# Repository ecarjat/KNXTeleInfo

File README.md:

# **French energy provider Enedis TeleInfo (TIC) KNX interface.**

Compatible with Enedis Linky meters in "Historic" mode, and "Blue" meters.

This is a fork of [etrinh software](https://github.com/etrinh/TeleInfoKNX) whose original design can be bought [here](https://www.tindie.com/products/zdi/knx-teleinfo/) 

This fork uses Raspberry [RP2040](https://www.raspberrypi.com/products/rp2040/) with a 64M-bit Serial Flash Memory and has a USB B Micro port to update the firmware.

# Firmware

The firmware has been refactored to split classes into their own files and adapt it to the rp2040.
It also leverages the latest version (as of 01/12/22) of [KNX Library](https://github.com/thelsing/knx) and in particular it's support for RP2040.

## **Features:**
- Activatable RealTime mode for real-time consumption monitoring/display.
- History of total Consumption (Current Year, Current Month, Today, Last Year, Last Month, Yesterday) (an external KNX Clock participant is required to provide accurate date and time).
- ETS5 configurable.
- Bus powered (10mA).

## **Usage:**
- Connect the device to the TeleInfo terminals (I1 I2) on the energy meter (No polarity).
- Connect the device to the KNX bus.
- To activate the device Programming Mode, click the "PROG / HRST".
- Configure device in ETS.
- To reset History, press the History Reset "PROG / HRST" Button more than 4 seconds.
- In case of over-current warning, the message "Depassement" (Group Object 43) is repeated every 10 seconds on the bus.

## **Led Interpretation:**
- Led Blinking (0.5s On/1.5s Off): TeleInfo data are receiving - **Device is working properly**.
- Led Continuously On: The device is in programming mode (it will automatically switch off after a delay of 15 minutes or a new press on the "PROG / HRST" button).
- Led Blinking (0.5s On/0.5s Off): The History is erased (happens when the "PROG / HRST" Button is pressed during more than 4 seconds).
- Led Off: The device is not receiving TeleInfo data, or is not configured with ETS5, or is not connected to the KNX Bus.

## **Group Objects:**
All "Consumption" Group Objects (from GO 7 to GO 24):

- Can be read to get the consumption index difference from the beginning and ending of the specified period.
- Can be written by the consumption index at the beginning of the corresponding period. It allows to specifically initialize the history from data provided by your energy provider. It is advised to set these indexes before affecting monitoring participants to these Group Objects.

## **Product Database:**
Click [here](https://github.com/etrinh/TeleInfoKNX/raw/master/ETS/teleinfo.knxprod) to download ETS5 product database (identified as KNX Association).

# Firmware upload
The Firmware can be uploaded directly through the USB port. On MacOS The firmware upload can be done by uncommenting this line in platform.io:
```
;upload_port = /Volumes/RPI-RP2/
```
This leverages the rp2040 embedded boot firmware. If the drive does not show pushing the reset button on the main board (SW3) while plugging in the usb should make it appear.
Once the firmware has been uploaded once, the serial port should become available.

# Hardware

## Sources
The hardware is build from a set of open source designs
[Adafruit ItsyBitsy rp2040](https://github.com/adafruit/Adafruit-ItsyBitsy-RP2040-PCB)
[Nano BCU](https://gitlab.com/knx-makerstuff/knx_microbcu2/-/wikis/NanoBCU)
[PiTInfo](https://github.com/hallard/teleinfo/tree/master/PiTInfo)
cobbled together on a board that needs to be cut in three parts and assembled.

## Geting the hardware

The folder hardware contain the kicad files and the gerber/bom/cpl files that can be sent to [JLCPCB](https://jlcpcb.com/).
The fabrication output is a board 

## Hardware assembly

The board then needs to be cut in three parts.

The assembly should be fairly self explanatory with teh silk screen. There are two unsused pins on the main board reserver for future use.

Once assembled the board looks like this

And fits into a [DIN Rail Box Size 1 from RS PRO](https://docs.rs-online.com/575c/A700000006545717.pdf). This can be ordered [here](https://fr.rs-online.com/web/p/boitiers-rail-din/1947577?cm_mmc=FR-PLA-DS3A-_-google-_-CSS_FR_FR_Boitiers_%26_coffrets_et_armoires_Whoop-_-(FR:Whoop!)+Bo%C3%AEtiers+rail+DIN-_-1947577&matchtype=&pla-305134126740&gclsrc=ds&gclsrc=ds).

## Remarks

The NeoPixel on the top board is not used by this application and is not powered by the firmware.

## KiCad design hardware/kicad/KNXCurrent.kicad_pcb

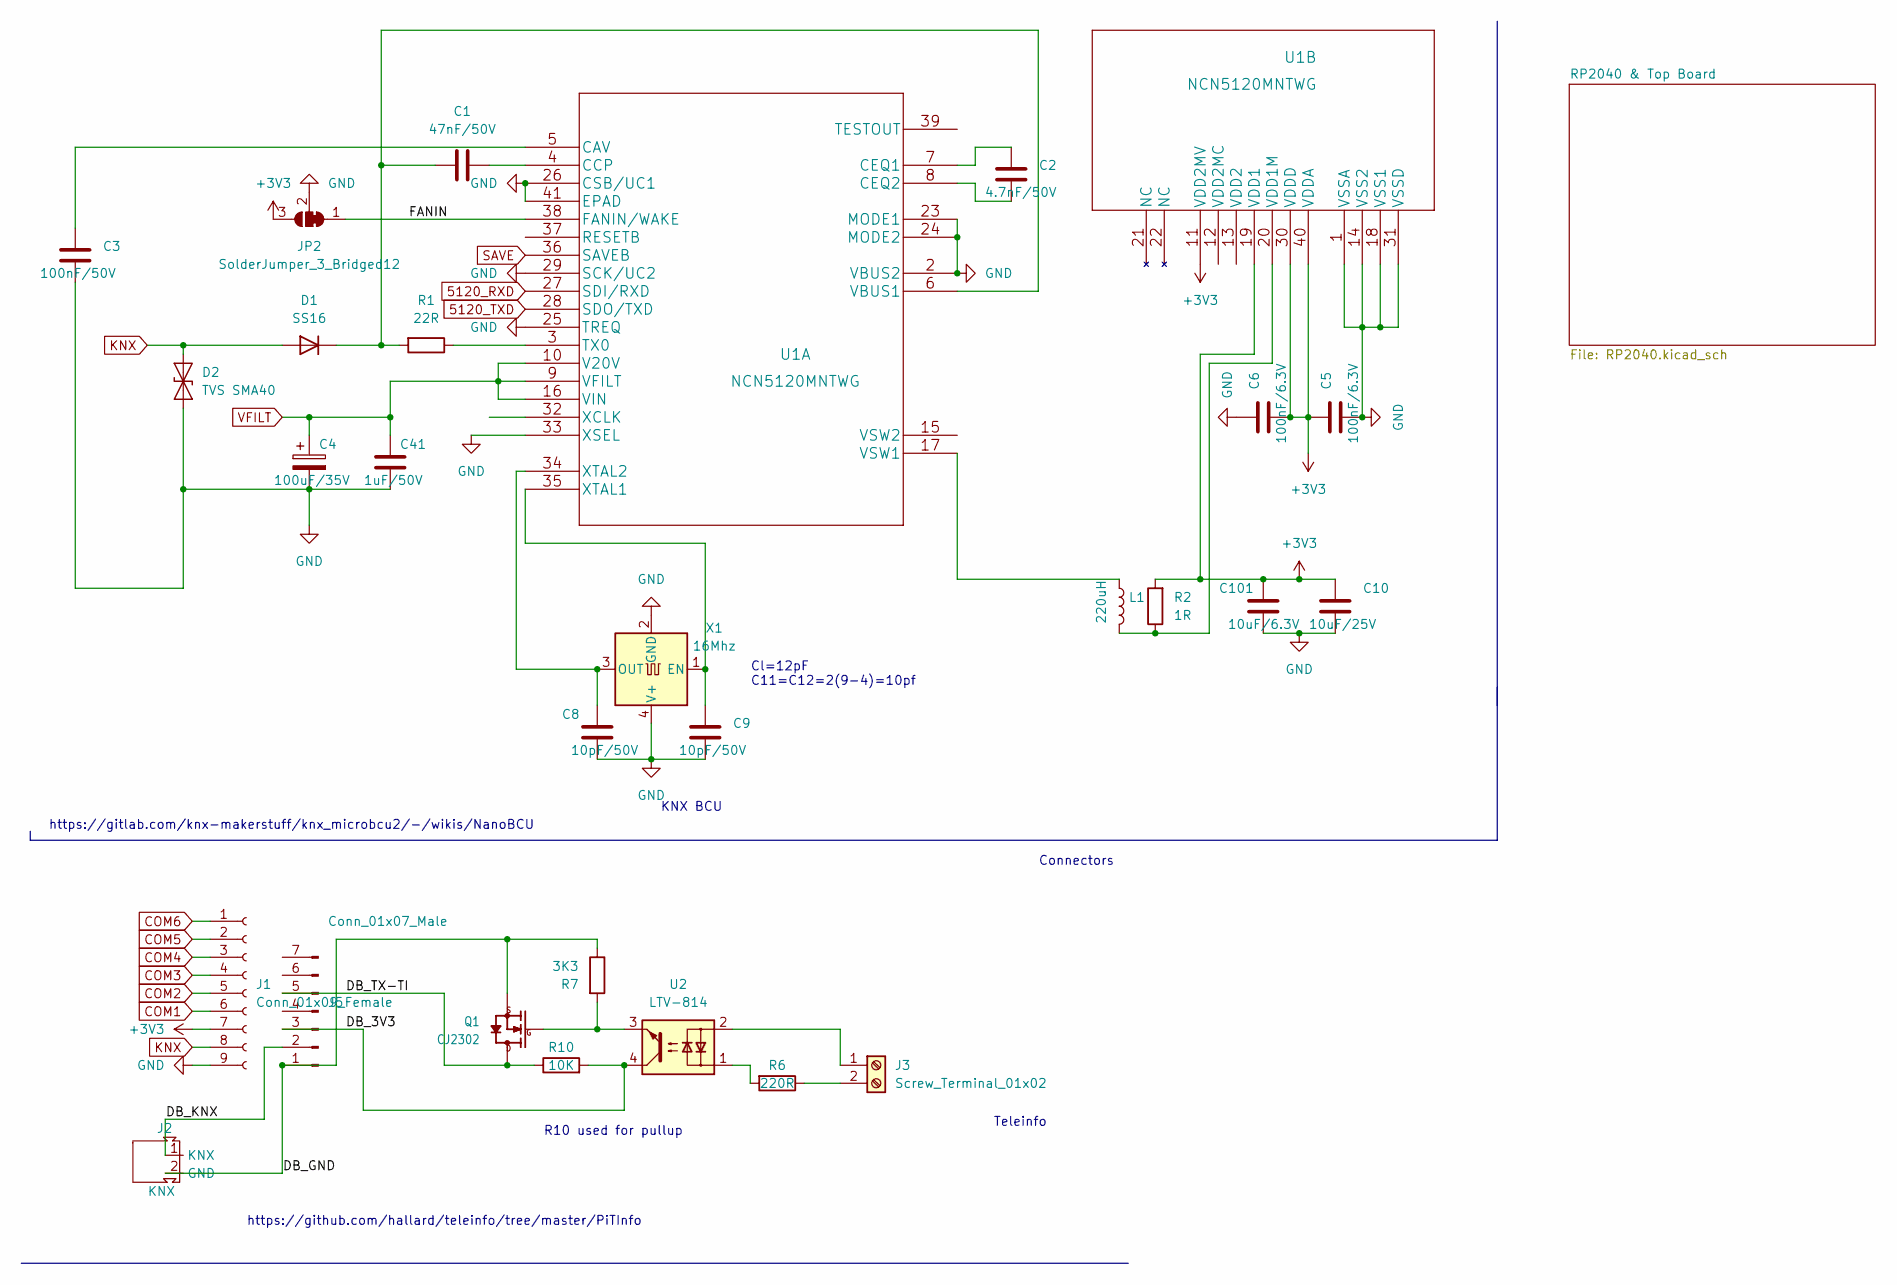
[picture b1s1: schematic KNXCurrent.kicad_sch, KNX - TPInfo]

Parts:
C1: 47nF/50V; C_0603_1608Metric; LCSC C1622
C2: 4.7nF/50V; C_0603_1608Metric; LCSC C53987
C3: 100nF/50V; C_0603_1608Metric; LCSC C14663
C4: 100uF/35V; CP_Elec_6.3x5.7; LCSC C249982
C5, C6: 100nF/6.3V; C_0402_1005Metric; LCSC C1525
C8, C9: 10pF/50V; C_0402_1005Metric; LCSC C32949
C10: 10uF/25V; C_0603_1608Metric; LCSC C96446
C41: 1uF/50V; C_0603_1608Metric; LCSC C15849
C101: 10uF/6.3V; C_0805_2012Metric; LCSC C15850
D1: SS16; D_SMA; LCSC C183023
D2: TVS SMA40; D_SMA; LCSC C513490
J1: Conn_01x09_Female; PinSocket_1x09_P2.54mm_Vertical
J2: KNX; KNX Male
J3: Screw_Terminal_01x02; TerminalBlock_Altech_AK300-2_P5.00mm
J5: Conn_01x07_Male; PinHeader_1x07_P2.54mm_Horizontal
JP2: SolderJumper_3_Bridged12; SolderJumper-3_P1.3mm_Bridged2Bar12_RoundedPad1.0x1.5mm_Num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
L1: 220uH; IND_VLS5045EX-3R3N; LCSC C501936
Q1: CJ2302; SOT-23; LCSC C2910175
R1: 22R; R_2512_6332Metric; LCSC C421606
R2: 1R; R_0402_1005Metric; LCSC C332612
R6: 220R; R_0805_2012Metric; LCSC C17557
R7: 3K3; R_0805_2012Metric; LCSC C26010
R10: 10K; R_0805_2012Metric; LCSC C17414
U1: NCN5120MNTWG; QFN-40-1EP_6x6mm_P0.5mm_EP4.6x4.6mm; LCSC C130364
U2: LTV-814; OPTO-SMD4; LCSC C125118
X1: 16Mhz; Crystal_SMD_3225-4Pin_3.2x2.5mm; LCSC C13738

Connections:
5120_RXD: U1.27 (SDI/RXD); also elsewhere on the board
5120_TXD: U1.28 (SDO/TXD); also elsewhere on the board
+3V3: C5.1, C6.2, C10.1, C101.1, J1.7, JP2.3 (B), R2.2, U1.11 (VDD2MV), U1.19 (VDD1), U1.30 (VDDD), U1.40 (VDDA); also elsewhere on the board
/DB_3V3: J5.3, R10.2, U2.4
/DB_GND: J2.2 (GND), J5.1, Q1.2 (S), R7.1
/DB_KNX: J2.1 (KNX), J5.2
/DB_TX-TI: J5.5, Q1.3 (D), R10.1
/FANIN: JP2.1 (A), U1.38 (FANIN/WAKE)
COM1: J1.6; also elsewhere on the board
COM2: J1.5; also elsewhere on the board
COM3: J1.4; also elsewhere on the board
COM4: J1.3; also elsewhere on the board
COM5: J1.2; also elsewhere on the board
COM6: J1.1; also elsewhere on the board
GND: C3.2, C4.2, C5.2, C6.1, C8.2, C9.2, C10.2, C41.2, C101.2, D2.2 (A2), J1.9, JP2.2 (C), U1.1 (VSSA), U1.2 (VBUS2), U1.14 (VSS2), U1.18 (VSS1), U1.23 (MODE1), U1.24 (MODE2), U1.25 (TREQ), U1.26 (CSB/UC1), U1.29 (SCK/UC2), U1.31 (VSSD), U1.33 (XSEL), U1.41 (EPAD), X1.2 (GND), X1.4 (V+); also elsewhere on the board
KNX: D1.2 (A), D2.1 (A1), J1.8
unnamed: C1.1, D1.1 (K), R1.2, U1.6 (VBUS1)
unnamed: C1.2, U1.4 (CCP)
unnamed: C2.1, U1.7 (CEQ1)
unnamed: C2.2, U1.8 (CEQ2)
unnamed: C3.1, U1.5 (CAV)
unnamed: C8.1, U1.34 (XTAL2), X1.3 (OUT)
unnamed: C9.1, U1.35 (XTAL1), X1.1 (EN)
unnamed: J3.1, U2.2
unnamed: J3.2, R6.1
unnamed: L1.1, U1.17 (VSW1)
unnamed: L1.2, R2.1, U1.20 (VDD1M)
unnamed: Q1.1 (G), R7.2, U2.3
unnamed: R1.1, U1.3 (TX0)
unnamed: R6.2, U2.1
SAVE: U1.36 (SAVEB); also elsewhere on the board
VFILT: C4.1, C41.1, U1.9 (VFILT), U1.10 (V20V), U1.16 (VIN)

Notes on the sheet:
Connectors
R10 used for pullup
https://github.com/hallard/teleinfo/tree/master/PiTInfo
Teleinfo
Cl=12pF C11=C12=2(9-4)=10pf
KNX BCU
https://gitlab.com/knx-makerstuff/knx_microbcu2/-/wikis/NanoBCU

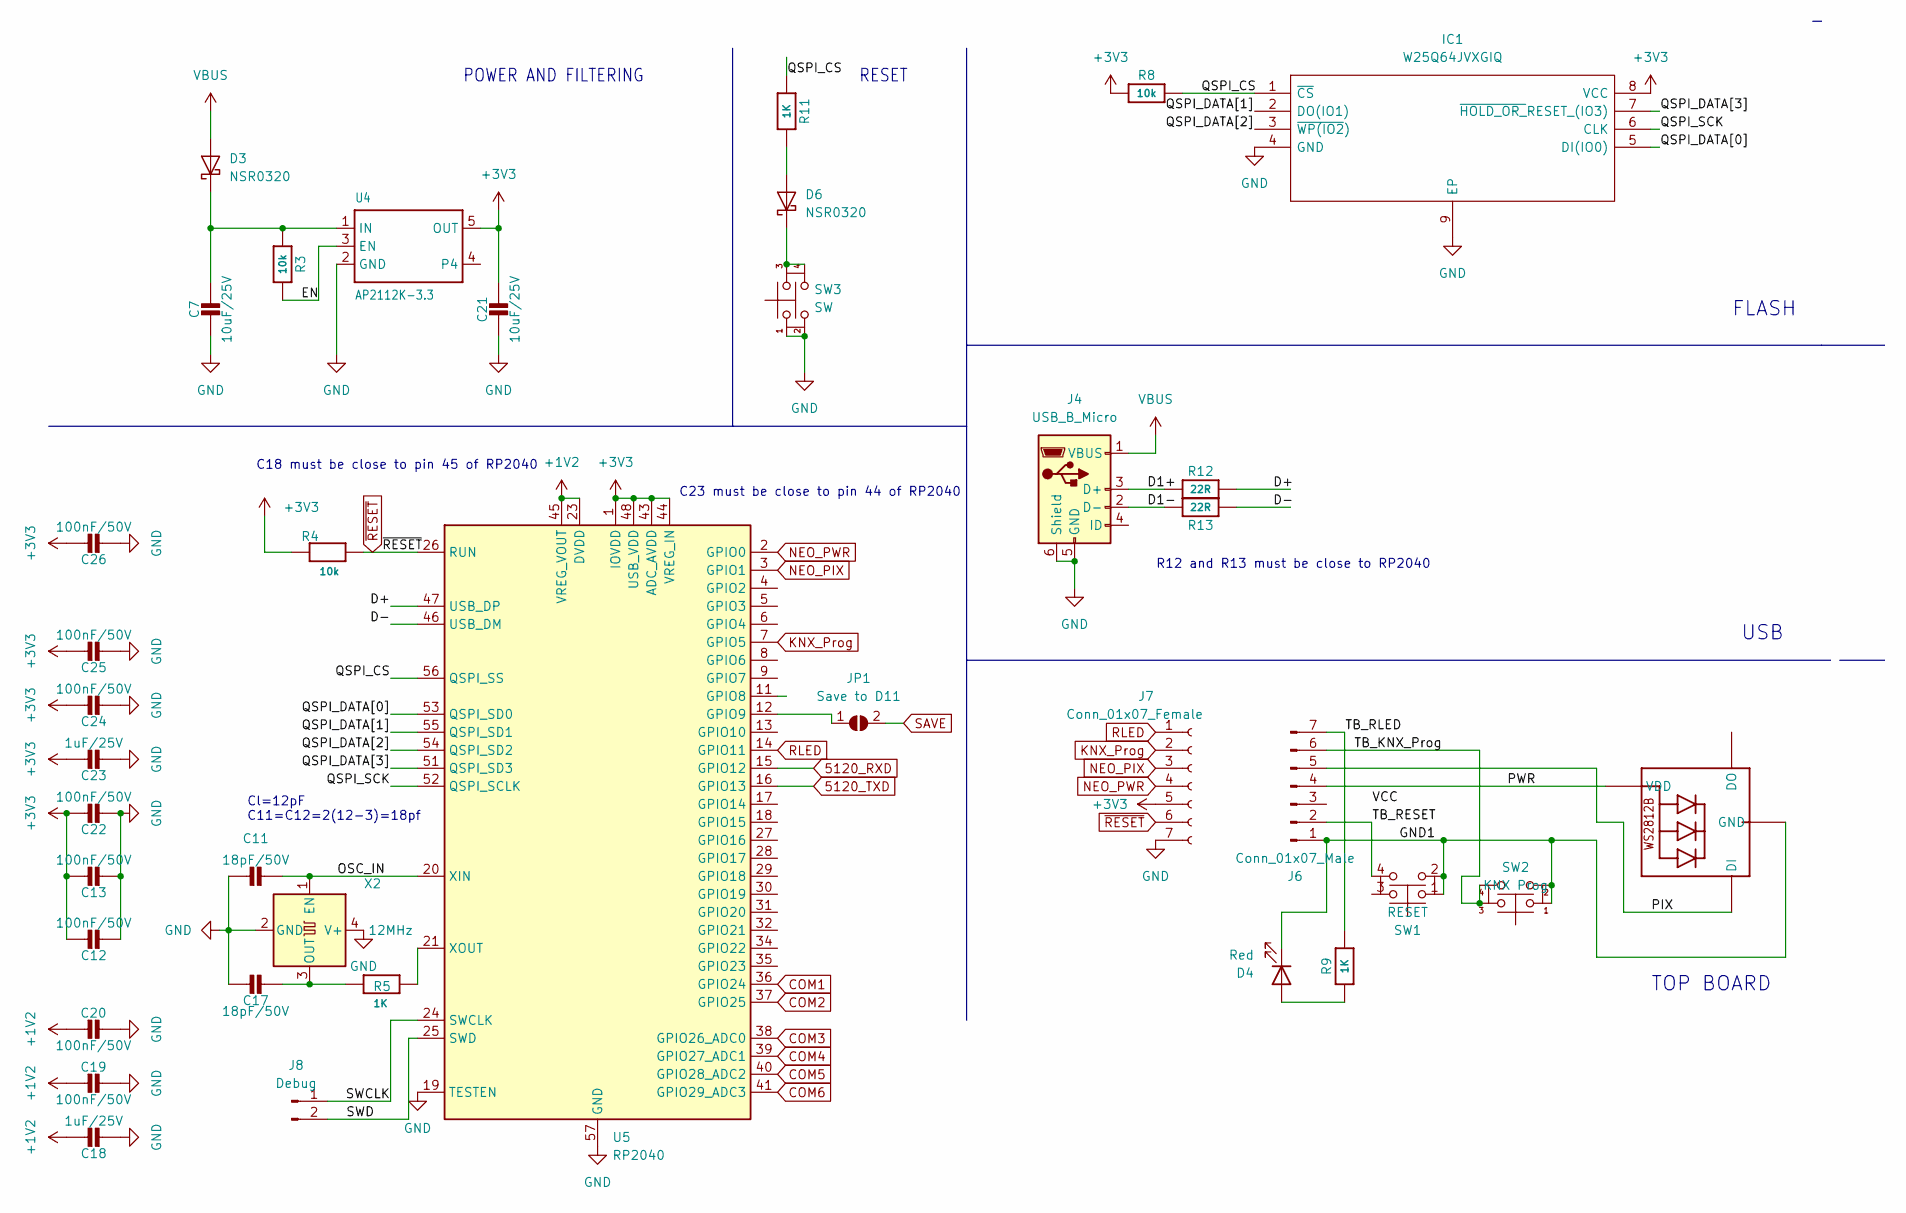
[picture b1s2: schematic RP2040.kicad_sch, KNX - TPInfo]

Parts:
C7, C21: 10uF/25V; C_0603_1608Metric; LCSC C96446
C11, C17: 18pF/50V; C_0402_1005Metric; LCSC C1549
C12, C13, C19, C20, C22, C24, C25, C26: 100nF/50V; C_0402_1005Metric; LCSC C307331
C18, C23: 1uF/25V; C_0402_1005Metric; LCSC C52923
D3, D6: NSR0320; D_SOD-323; LCSC C48192
D4: Red; D_0603_1608Metric; LCSC C2286
IC1: W25Q64JVXGIQ; SON80P400X400X50-9N; Manufacturer_Part_Number W25Q64JVXGIQ; LCSC C2940195
J4: USB_B_Micro; USB_Micro-B_Molex-105017-0001; LCSC C136000
J6: Conn_01x07_Male; PinHeader_1x07_P2.54mm_Horizontal
J7: Conn_01x07_Female; PinSocket_1x07_P2.54mm_Vertical
J8: Debug; PinHeader_1x02_P2.54mm_Vertical
JP1: Save to D11; SolderJumper-2_P1.3mm_Open_RoundedPad1.0x1.5mm
LED1: WS2812B3535; LED_WS2812B_PLCC4_5.0x5.0mm_P3.2mm; LCSC C2920042
R3, R4, R8: 10k; R_0402_1005Metric; LCSC C25744
R5, R9, R11: 1K; R_0402_1005Metric; LCSC C11702
R12, R13: 22R; R_0402_1005Metric; LCSC C25092
SW1: RESET; SW_TS-1187A-B-A-B; LCSC C318884
SW2: KNX Prog; SW_TS-1187A-B-A-B; LCSC C318884
SW3: SW; SW_TS-1187A-B-A-B; LCSC C318884
U4: AP2112K-3.3; SOT-23-5; LCSC C51118
U5: RP2040; QFN-56-1EP_7x7mm_P0.4mm_EP3.2x3.2mm; LCSC C2040
X2: 12MHz; Crystal_SMD_2520-4Pin_2.5x2.0mm; LCSC C521567

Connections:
5120_RXD: U5.15 (GPIO12); also elsewhere on the board
5120_TXD: U5.16 (GPIO13); also elsewhere on the board
+1V2: C18.1, C19.2, C20.2, U5.23 (DVDD), U5.45 (VREG_VOUT), U5.50 (DVDD)
+3V3: C12.1, C13.1, C21.1, C22.1, C23.1, C24.1, C25.1, C26.1, IC1.8 (VCC), J7.5, R4.1, R8.1, U4.5 (OUT), U5.1 (IOVDD), U5.10 (IOVDD), U5.22 (IOVDD), U5.33 (IOVDD), U5.42 (IOVDD), U5.43 (ADC_AVDD), U5.44 (VREG_IN), U5.48 (USB_VDD), U5.49 (IOVDD); also elsewhere on the board
/RP2040 & Top Board/D1+: J4.3 (D+), R12.1
/RP2040 & Top Board/D1-: J4.2 (D-), R13.1
/RP2040 & Top Board/D+: R12.2, U5.47 (USB_DP)
/RP2040 & Top Board/D-: R13.2, U5.46 (USB_DM)
/RP2040 & Top Board/EN: R3.2, U4.3 (EN)
/RP2040 & Top Board/GND1: D4.1 (K), J6.1, LED1.3 (GND), SW1.1, SW1.2, SW2.1, SW2.2
/RP2040 & Top Board/OSC_IN: C11.2, U5.20 (XIN), X2.1 (EN)
/RP2040 & Top Board/PIX: J6.5, LED1.4 (DI)
/RP2040 & Top Board/PWR: J6.4, LED1.1 (VDD)
/RP2040 & Top Board/QSPI_CS: IC1.1 (~CS), R8.2, R11.1, U5.56 (QSPI_SS)
/RP2040 & Top Board/QSPI_DATA[0]: IC1.5 (DI(IO0)), U5.53 (QSPI_SD0)
/RP2040 & Top Board/QSPI_DATA[1]: IC1.2 (DO(IO1)), U5.55 (QSPI_SD1)
/RP2040 & Top Board/QSPI_DATA[2]: IC1.3 (~WP(IO2)), U5.54 (QSPI_SD2)
/RP2040 & Top Board/QSPI_DATA[3]: IC1.7 (~HOLD_OR_RESET_(IO3)), U5.51 (QSPI_SD3)
/RP2040 & Top Board/QSPI_SCK: IC1.6 (CLK), U5.52 (QSPI_SCLK)
/RP2040 & Top Board/SWCLK: J8.1, U5.24 (SWCLK)
/RP2040 & Top Board/SWD: J8.2, U5.25 (SWD)
/RP2040 & Top Board/TB_KNX_Prog: J6.6, SW2.3, SW2.4
/RP2040 & Top Board/TB_RESET: J6.2, SW1.4
/RP2040 & Top Board/TB_RLED: J6.7, R9.2
COM1: U5.36 (GPIO24); also elsewhere on the board
COM2: U5.37 (GPIO25); also elsewhere on the board
COM3: U5.38 (GPIO26_ADC0); also elsewhere on the board
COM4: U5.39 (GPIO27_ADC1); also elsewhere on the board
COM5: U5.40 (GPIO28_ADC2); also elsewhere on the board
COM6: U5.41 (GPIO29_ADC3); also elsewhere on the board
GND: C7.2, C11.1, C12.2, C13.2, C17.1, C18.2, C19.1, C20.1, C21.2, C22.2, C23.2, C24.2, C25.2, C26.2, IC1.4 (GND), IC1.9 (EP), J4.5 (GND), J4.6 (Shield), J7.7, SW3.1, SW3.2, U4.2 (GND), U5.19 (TESTEN), U5.57 (GND), X2.2 (GND), X2.4 (V+); also elsewhere on the board
KNX_Prog: J7.2, U5.7 (GPIO5)
NEO_PIX: J7.3, U5.3 (GPIO1)
NEO_PWR: J7.4, U5.2 (GPIO0)
unnamed: C7.1, D3.1 (K), R3.1, U4.1 (IN)
unnamed: C17.2, R5.1, X2.3 (OUT)
unnamed: D4.2 (A), R9.1
unnamed: D6.1 (K), SW3.3, SW3.4
unnamed: D6.2 (A), R11.2
unnamed: JP1.1 (A), U5.12 (GPIO9)
unnamed: R5.2, U5.21 (XOUT)
RLED: J7.1, U5.14 (GPIO11)
SAVE: JP1.2 (B); also elsewhere on the board
VBUS: D3.2 (A), J4.1 (VBUS)
~RESET: J7.6, R4.2, U5.26 (RUN)

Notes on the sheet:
C23 must be close to pin 44 of RP2040
POWER AND FILTERING
R12 and R13 must be close to RP2040
USB
C18 must be close to pin 45 of RP2040
TOP BOARD
Cl=12pF C11=C12=2(12-3)=18pf
FLASH
RESET

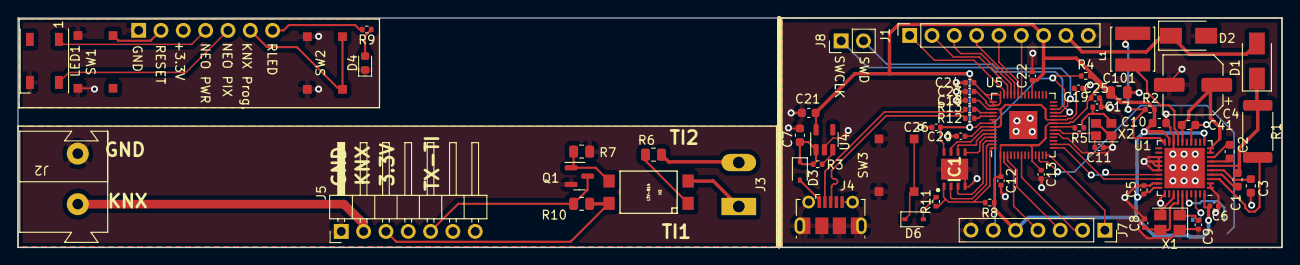
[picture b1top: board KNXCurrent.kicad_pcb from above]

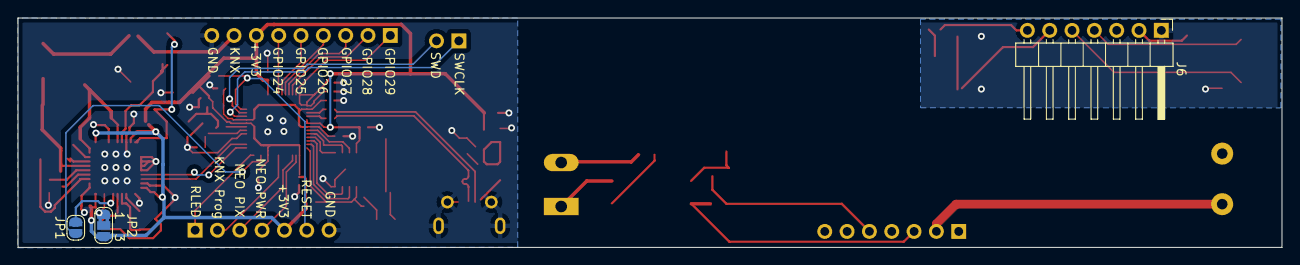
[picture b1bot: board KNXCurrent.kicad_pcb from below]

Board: 2 copper layers, 143.8 x 26.1 mm, 66 parts (3 on the bottom side), 66 nets.

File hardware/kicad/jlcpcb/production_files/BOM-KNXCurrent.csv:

Comment,Designator,Footprint,LCSC
16Mhz,X1,Crystal_SMD_3225-4Pin_3.2x2.5mm, C13738
100nF/50V,C3,C_0603_1608Metric, C14663
AP2112K-3.3,U4,SOT-23-5, C51118
TVS SMA40,D2,D_SMA, C513490
1K,"R11,R5,R9",R_0402_1005Metric,C11702
LTV-814,U2,OPTO-SMD4,C125118
NCN5120MNTWG,U1,QFN-40-1EP_6x6mm_P0.5mm_EP4.6x4.6mm,C130364
USB_B_Micro,J4,USB_Micro-B_Molex-105017-0001,C136000
100nF/6.3V,"C5,C6",C_0402_1005Metric,C1525
18pF/50V,"C11,C17",C_0402_1005Metric,C1549
1uF/50V,C41,C_0603_1608Metric,C15849
10uF/6.3V,C101,C_0805_2012Metric,C15850
47nF/50V,C1,C_0603_1608Metric,C1622
10K,R10,R_0805_2012Metric,C17414
220R,R6,R_0805_2012Metric,C17557
SS16,D1,D_SMA,C183023
RP2040,U5,QFN-56-1EP_7x7mm_P0.4mm_EP3.2x3.2mm,C2040
Red,D4,D_0603_1608Metric,C2286
100uF/35V,C4,CP_Elec_6.3x5.7,C249982
22R,"R12,R13",R_0402_1005Metric,C25092
10k,"R3,R4,R8",R_0402_1005Metric,C25744
3K3,R7,R_0805_2012Metric,C26010
CJ2302,Q1,SOT-23,C2910175
WS2812B3535,LED1,LED_WS2812B_PLCC4_5.0x5.0mm_P3.2mm,C2920042
W25Q64JVXGIQ,IC1,SON80P400X400X50-9N,C2940195
100nF/50V,"C12,C13,C19,C20,C22,C24,C25,C26",C_0402_1005Metric,C307331
RESET,"SW1,SW2,SW3",SW_TS-1187A-B-A-B,C318884
10pF/50V,"C8,C9",C_0402_1005Metric,C32949
1R,R2,R_0402_1005Metric,C332612
22R,R1,R_2512_6332Metric,C421606
NSR0320,"D3,D6",D_SOD-323,C48192
220uH,L1,IND_VLS5045EX-3R3N,C501936
12MHz,X2,Crystal_SMD_2520-4Pin_2.5x2.0mm,C521567
1uF/25V,"C18,C23",C_0402_1005Metric,C52923
4.7nF/50V,C2,C_0603_1608Metric,C53987
10uF/25V,"C10,C21,C7",C_0603_1608Metric,C96446
Debug,J8,PinHeader_1x02_P2.54mm_Vertical,
Conn_01x07_Male,J5,PinHeader_1x07_P2.54mm_Horizontal,
Conn_01x07_Female,J7,PinSocket_1x07_P2.54mm_Vertical,
KNX,J2,KNX Male,
Screw_Terminal_01x02,J3,TerminalBlock_Altech_AK300-2_P5.00mm,
Conn_01x09_Female,J1,PinSocket_1x09_P2.54mm_Vertical,
Conn_01x07_Male,J6,PinHeader_1x07_P2.54mm_Horizontal,
SolderJumper_3_Bridged12,JP2,SolderJumper-3_P1.3mm_Bridged2Bar12_RoundedPad1.0x1.5mm_NumberLabels,
Save to D11,JP1,SolderJumper-2_P1.3mm_Open_RoundedPad1.0x1.5mm,

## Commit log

2022-12-01 moved classes in their separate files and updated platformio.ini for rp2040
2022-12-01 changed knx submodule
2022-12-01 vscode cleanup
2022-12-01 Added progmode timeout and history back in
2022-12-01 initial hardware commit
2022-12-01 Changed README
2022-12-01 typos
2022-12-01 Updated images links
2022-12-01 Ignore Docs folder
